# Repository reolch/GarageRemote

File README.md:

# GarageRemote
三和製電動シャッターをESP32で開閉するためのプロジェクト

## 回路図

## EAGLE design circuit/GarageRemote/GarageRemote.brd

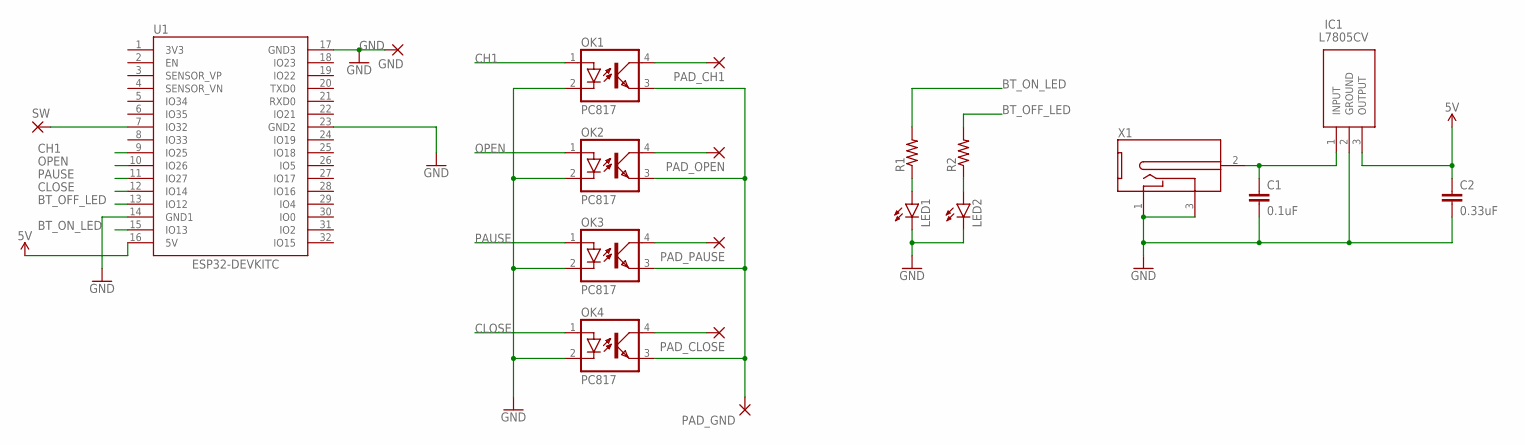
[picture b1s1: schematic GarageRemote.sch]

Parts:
C1: 0.1uF; C2.5-2
C2: 0.33uF; C2.5-2
GND: 2,54/1,0
IC1: L7805CV; TO255P460X1020X2008-3P
LED1, LED2: LED5MM
OK1, OK2, OK3, OK4: PC817; DIL04
PAD_CH1: 2,54/1,0
PAD_CLOSE: 2,54/1,0
PAD_GND: 2,54/1,0
PAD_OPEN: 2,54/1,0
PAD_PAUSE: 2,54/1,0
R1, R2: R-US_0204/5; 0204/5
SW: 2,54/1,0
U1: ESP32-DEVKITC; MODULE_ESP32-DEVKITC
X1: DC-2.1MM-5MM; DC-21MM

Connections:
3V3: U1.1 (3V3)
5V: C2.1, IC1.3 (OUTPUT), U1.16 (5V)
BT_OFF_LED: R2.2, U1.13 (IO12)
BT_ON_LED: R1.2, U1.15 (IO13)
CH1: OK1.1 (A), U1.9 (IO25)
CLOSE: OK4.1 (A), U1.12 (IO14)
GND: C1.2, C2.2, GND.1, IC1.2 (GROUND), LED1.K (C), LED2.K (C), OK1.2 (C), OK2.2 (C), OK3.2 (C), OK4.2 (C), U1.14 (GND1), U1.17 (GND3), U1.23 (GND2), X1.1, X1.3 (2)
unnamed: OK1.3 (EMIT), OK2.3 (EMIT), OK3.3 (EMIT), OK4.3 (EMIT), PAD_GND.1
unnamed: OK2.4 (COL), PAD_OPEN.1
unnamed: OK1.4 (COL), PAD_CH1.1
unnamed: OK3.4 (COL), PAD_PAUSE.1
unnamed: OK4.4 (COL), PAD_CLOSE.1
unnamed: SW.1, U1.7 (IO32)
unnamed: LED2.A, R2.1
unnamed: C1.1, IC1.1 (INPUT), X1.2 (3)
unnamed: LED1.A, R1.1
OPEN: OK2.1 (A), U1.10 (IO26)
PAUSE: OK3.1 (A), U1.11 (IO27)

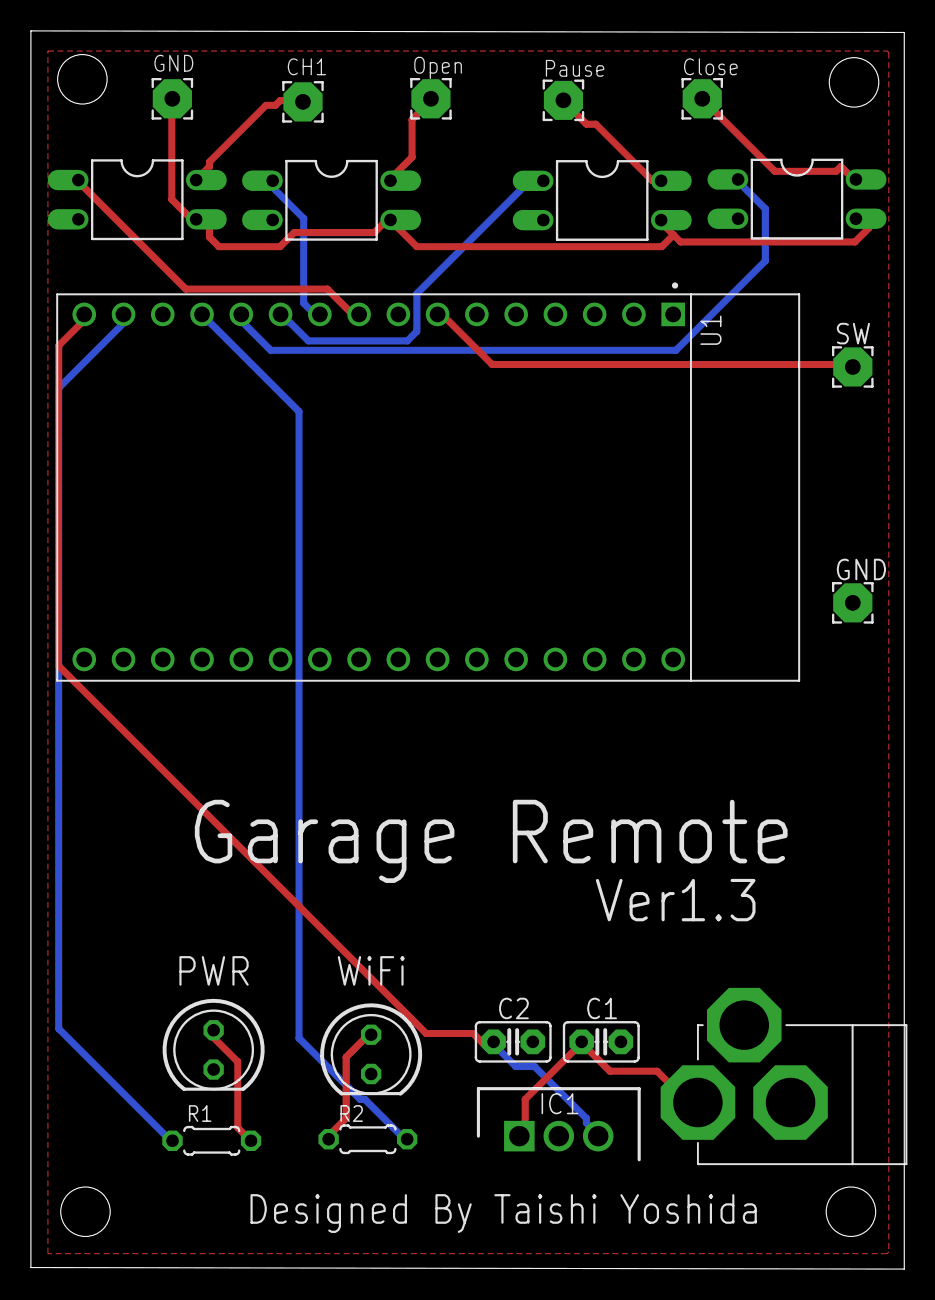
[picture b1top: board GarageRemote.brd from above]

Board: 2 copper layers, 56.5 x 80.1 mm, 20 parts (0 on the bottom side), 17 nets.

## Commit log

2022-09-20 Ver1.0 作成したプロジェクトをコミットする
2022-10-19 ESP32モジュールのライブラリを修正しました。
2022-10-19 Arduino側のコードを作成
2022-10-19 基盤を修正しました。 DCJackを変更しました。 SWのPadを追加しました。
2022-11-03 Ver1.3に改修しました。

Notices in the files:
parts and their libraries:
FaBo-Supply: Released under the Creative Commons Attribution-ShareAlike 4.0 License
https://creativecommons.org/licenses/by-sa/4.0
